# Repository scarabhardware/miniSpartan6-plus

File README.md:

# miniSpartan6-plus

## programming

```sh
# program fpga
xc3sprog -c ftdi dvid_serdes.bit
# program SPI flash
xc3sprog -c ftdi bscan_spi_s6lx9_ftg256.bit
xc3sprog -c ftdi -I dvid_serdes.bit
```

## references

 - http://www.scarabhardware.com
 - http://hamsterworks.co.nz/mediawiki/index.php/FPGA_Projects
 - https://github.com/timvideos/HDMI2USB

## board pinout

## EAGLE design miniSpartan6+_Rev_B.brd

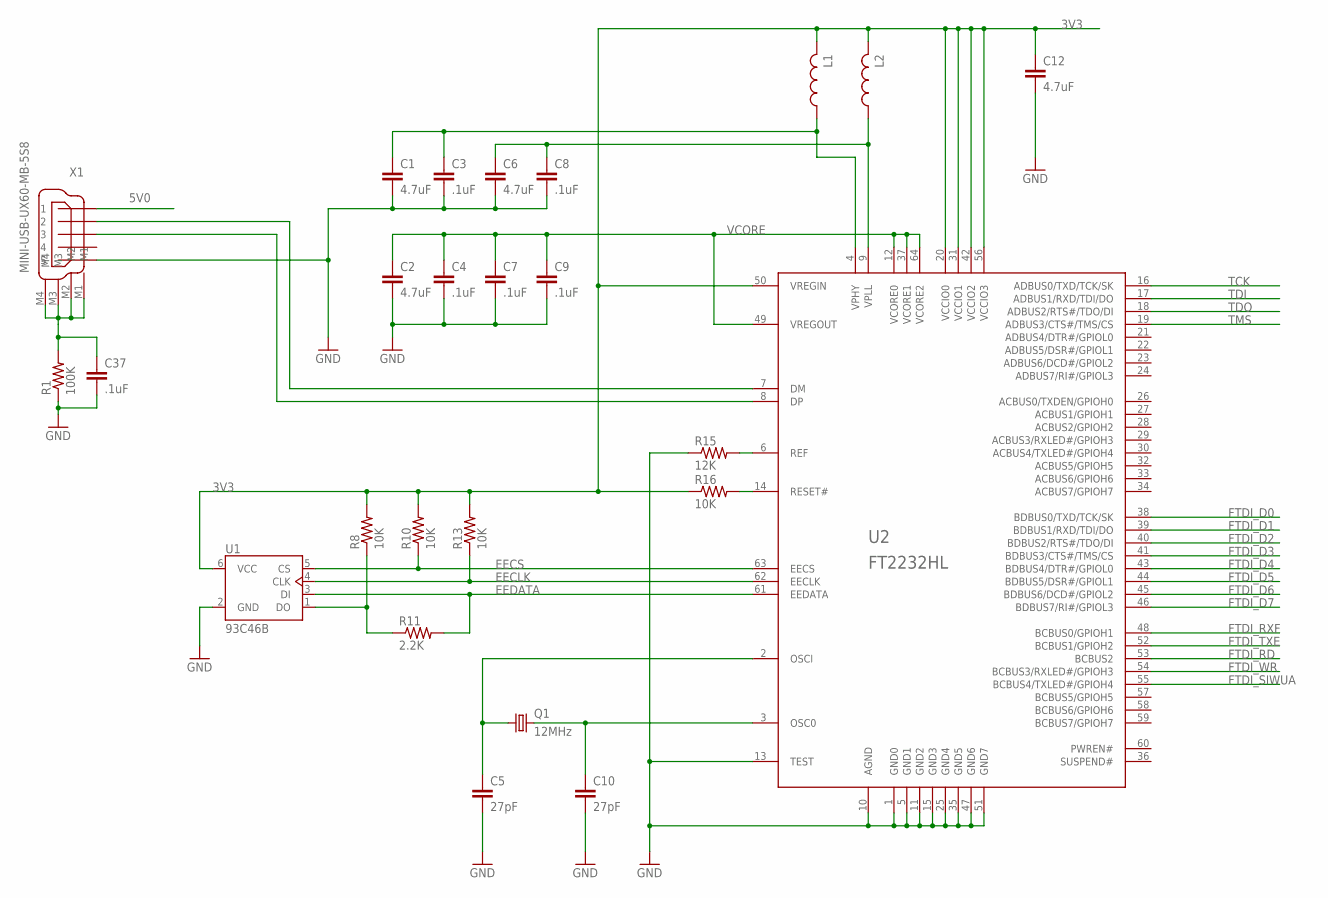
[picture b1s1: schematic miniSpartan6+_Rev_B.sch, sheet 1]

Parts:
C1, C2, C6, C12: 4.7uF; C0603K
C3, C4, C7, C8, C9, C37: .1uF; C0603K
C5, C10: 27pF; C0603K
L1, L2: L-USL2012C; L2012C
Q1: 12MHz; CRYSTAL3.2X2.5MM
R1: 100K; R0603
R8, R10, R13, R16: 10K; R0603
R11: 2.2K; R0603
R15: 12K; R0603
U1: 93C46B; SOT23-6
U2: FT2232HL; LQFP64
X1: MINI-USB-UX60-MB-5S8; UX60-MB-5S8

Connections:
3V3: C12.1, L1.2, L2.2, R8.2, R10.2, R13.2, R16.1, U1.6 (VCC), U2.20 (VCCIO0), U2.31 (VCCIO1), U2.42 (VCCIO2), U2.50 (VREGIN), U2.56 (VCCIO3); also elsewhere on the board
5V0: X1.1; also elsewhere on the board
EECLK: R13.1, U1.4 (CLK), U2.62 (EECLK)
EECS: R10.1, U1.5 (CS), U2.63 (EECS)
EEDATA: R11.2, U1.3 (DI), U2.61 (EEDATA)
FTDI_D0: U2.38 (BDBUS0/TXD/TCK/SK); also elsewhere on the board
FTDI_D1: U2.39 (BDBUS1/RXD/TDI/DO); also elsewhere on the board
FTDI_D2: U2.40 (BDBUS2/RTS#/TDO/DI); also elsewhere on the board
FTDI_D3: U2.41 (BDBUS3/CTS#/TMS/CS); also elsewhere on the board
FTDI_D4: U2.43 (BDBUS4/DTR#/GPIOL0); also elsewhere on the board
FTDI_D5: U2.44 (BDBUS5/DSR#/GPIOL1); also elsewhere on the board
FTDI_D6: U2.45 (BDBUS6/DCD#/GPIOL2); also elsewhere on the board
FTDI_D7: U2.46 (BDBUS7/RI#/GPIOL3); also elsewhere on the board
FTDI_RD: U2.53 (BCBUS2); also elsewhere on the board
FTDI_RXF: U2.48 (BCBUS0/GPIOH1); also elsewhere on the board
FTDI_SIWUA: U2.55 (BCBUS4/TXLED#/GPIOH4); also elsewhere on the board
FTDI_TXE: U2.52 (BCBUS1/GPIOH2); also elsewhere on the board
FTDI_WR: U2.54 (BCBUS3/RXLED#/GPIOH3); also elsewhere on the board
GND: C1.2, C2.2, C3.2, C4.2, C5.2, C6.2, C7.2, C8.2, C9.2, C10.2, C12.2, C37.2, R1.1, R15.1, U1.2 (GND), U2.1 (GND0), U2.5 (GND1), U2.10 (AGND), U2.11 (GND2), U2.13 (TEST), U2.15 (GND3), U2.25 (GND4), U2.35 (GND5), U2.47 (GND6), U2.51 (GND7), X1.5; also elsewhere on the board
unnamed: U2.7 (DM), X1.2
unnamed: C37.1, R1.2, X1.M1, X1.M2, X1.M3, X1.M4
unnamed: U2.8 (DP), X1.3
unnamed: C5.1, Q1.1, U2.2 (OSCI)
unnamed: C10.1, Q1.3 (2), U2.3 (OSC0)
unnamed: C6.1, C8.1, L2.1, U2.9 (VPLL)
unnamed: R16.2, U2.14 (RESET#)
unnamed: R15.2, U2.6 (REF)
unnamed: C1.1, C3.1, L1.1, U2.4 (VPHY)
unnamed: R8.1, R11.1, U1.1 (DO)
TCK: U2.16 (ADBUS0/TXD/TCK/SK); also elsewhere on the board
TDI: U2.17 (ADBUS1/RXD/TDI/DO); also elsewhere on the board
TDO: U2.18 (ADBUS2/RTS#/TDO/DI); also elsewhere on the board
TMS: U2.19 (ADBUS3/CTS#/TMS/CS); also elsewhere on the board
VCORE: C2.1, C4.1, C7.1, C9.1, U2.12 (VCORE0), U2.37 (VCORE1), U2.49 (VREGOUT), U2.64 (VCORE2)

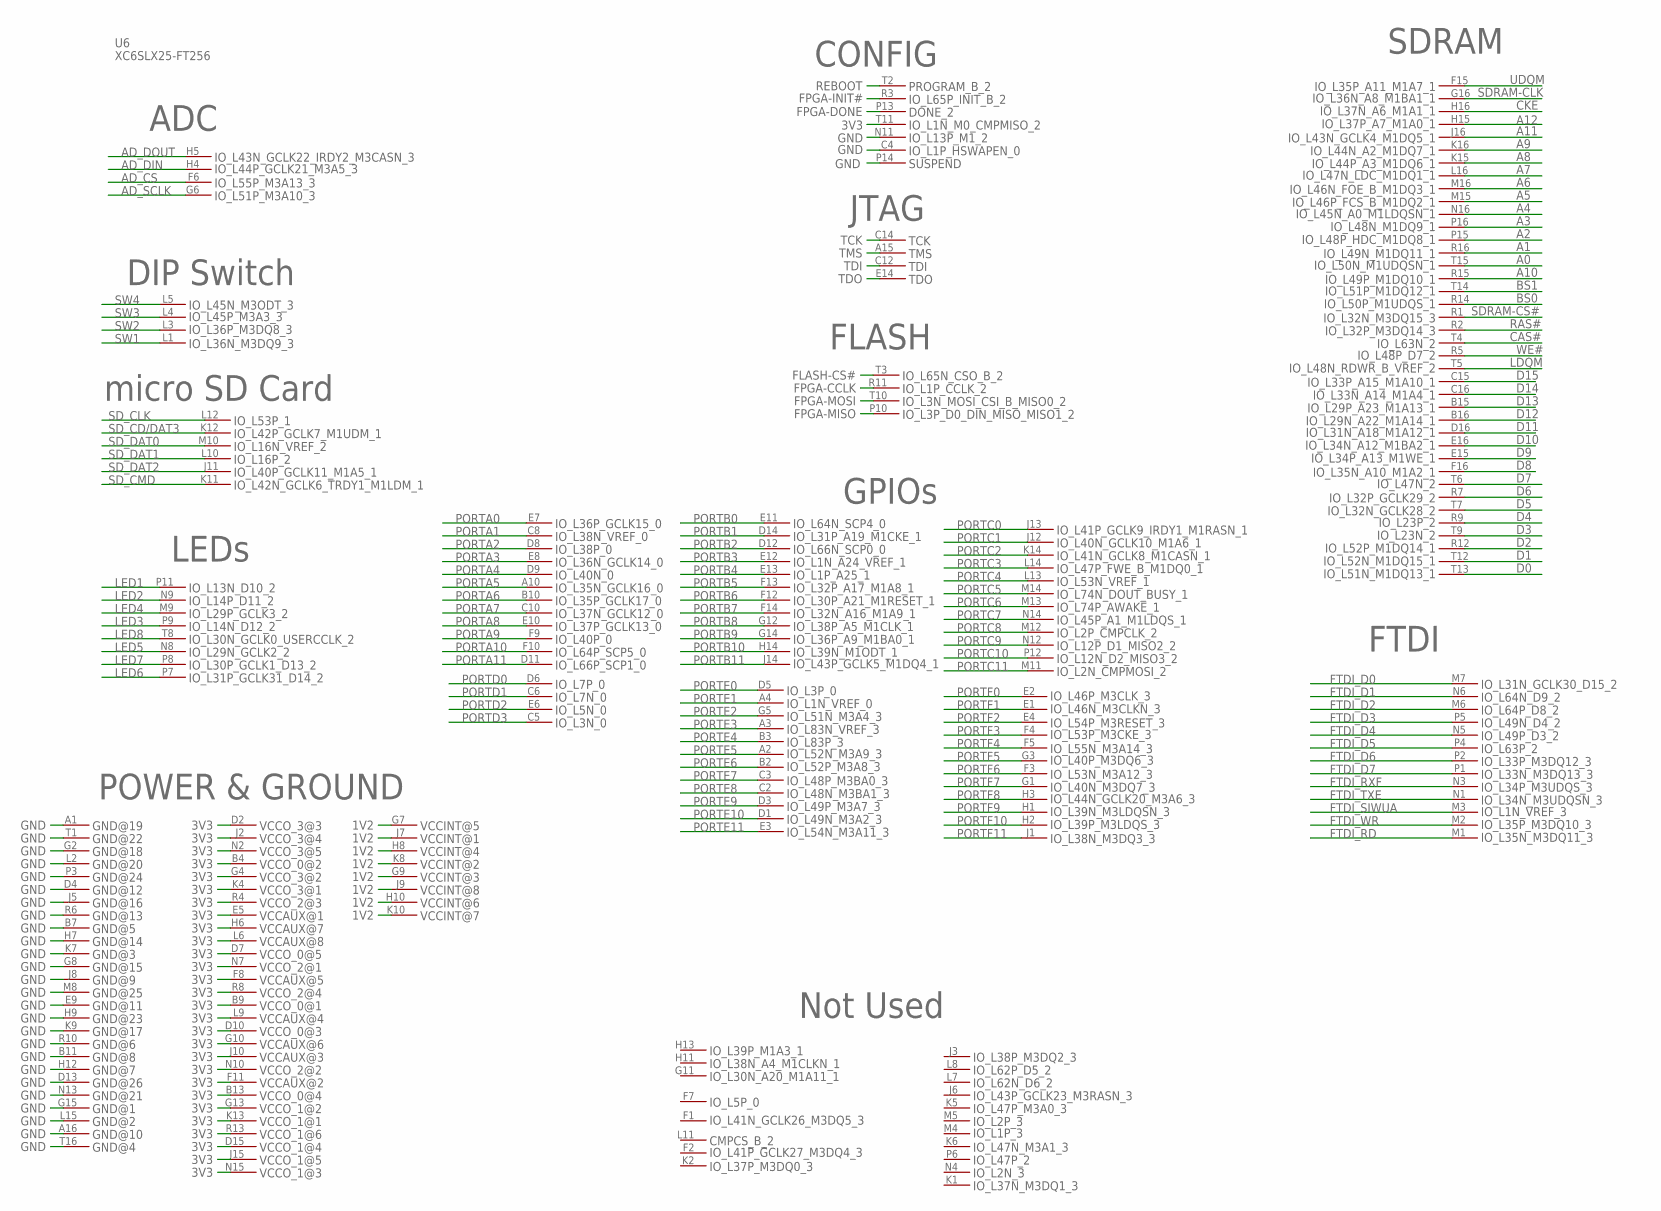
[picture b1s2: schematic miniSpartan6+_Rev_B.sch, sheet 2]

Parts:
U6: XC6SLX25-FT256; XILINX-FT256; DIGIKEY# 122-1753-ND

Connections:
1V2: U6.G7, U6.G9, U6.H8, U6.H10, U6.J7, U6.J9, U6.K8, U6.K10; also elsewhere on the board
3V3: U6.B4, U6.B9, U6.B13, U6.D2, U6.D7, U6.D10, U6.D15, U6.E5, U6.F8, U6.F11, U6.G4, U6.G10, U6.G13, U6.H6, U6.J2, U6.J10, U6.J15, U6.K4, U6.K13, U6.L6, U6.L9, U6.N2, U6.N7, U6.N10, U6.N15, U6.R4, U6.R8, U6.R13, U6.T11; also elsewhere on the board
A0: U6.T15; also elsewhere on the board
A1: U6.R16; also elsewhere on the board
A2: U6.P15; also elsewhere on the board
A3: U6.P16; also elsewhere on the board
A4: U6.N16; also elsewhere on the board
A5: U6.M15; also elsewhere on the board
A6: U6.M16; also elsewhere on the board
A7: U6.L16; also elsewhere on the board
A8: U6.K15; also elsewhere on the board
A9: U6.K16; also elsewhere on the board
A10: U6.R15; also elsewhere on the board
A11: U6.J16; also elsewhere on the board
A12: U6.H15; also elsewhere on the board
AD_CS: U6.F6; also elsewhere on the board
AD_DIN: U6.H4; also elsewhere on the board
AD_DOUT: U6.H5; also elsewhere on the board
AD_SCLK: U6.G6; also elsewhere on the board
BS0: U6.R14; also elsewhere on the board
BS1: U6.T14; also elsewhere on the board
CAS#: U6.T4; also elsewhere on the board
CKE: U6.H16; also elsewhere on the board
D0: U6.T13; also elsewhere on the board
D1: U6.T12; also elsewhere on the board
D2: U6.R12; also elsewhere on the board
D3: U6.T9; also elsewhere on the board
D4: U6.R9; also elsewhere on the board
D5: U6.T7; also elsewhere on the board
D6: U6.R7; also elsewhere on the board
D7: U6.T6; also elsewhere on the board
D8: U6.F16; also elsewhere on the board
D9: U6.E15; also elsewhere on the board
D10: U6.E16; also elsewhere on the board
D11: U6.D16; also elsewhere on the board
D12: U6.B16; also elsewhere on the board
D13: U6.B15; also elsewhere on the board
D14: U6.C16; also elsewhere on the board
D15: U6.C15; also elsewhere on the board
FLASH-CS#: U6.T3; also elsewhere on the board
FPGA-CCLK: U6.R11; also elsewhere on the board
FPGA-DONE: U6.P13
FPGA-INIT#: U6.R3
FPGA-MISO: U6.P10; also elsewhere on the board
FPGA-MOSI: U6.T10; also elsewhere on the board
FTDI_D0: U6.M7; also elsewhere on the board
FTDI_D1: U6.N6; also elsewhere on the board
FTDI_D2: U6.M6; also elsewhere on the board
FTDI_D3: U6.P5; also elsewhere on the board
FTDI_D4: U6.N5; also elsewhere on the board
FTDI_D5: U6.P4; also elsewhere on the board
FTDI_D6: U6.P2; also elsewhere on the board
FTDI_D7: U6.P1; also elsewhere on the board
FTDI_RD: U6.M1; also elsewhere on the board
FTDI_RXF: U6.N3; also elsewhere on the board
FTDI_SIWUA: U6.M3; also elsewhere on the board
FTDI_TXE: U6.N1; also elsewhere on the board
FTDI_WR: U6.M2; also elsewhere on the board
GND: U6.A1, U6.A16, U6.B7, U6.B11, U6.C4, U6.D4, U6.D13, U6.E9, U6.G2, U6.G8, U6.G15, U6.H7, U6.H9, U6.H12, U6.J5, U6.J8, U6.K7, U6.K9, U6.L2, U6.L15, U6.M8, U6.N11, U6.N13, U6.P3, U6.P14, U6.R6, U6.R10, U6.T1, U6.T16; also elsewhere on the board
LDQM: U6.T5; also elsewhere on the board
LED1: U6.P11; also elsewhere on the board
LED2: U6.N9; also elsewhere on the board
LED3: U6.P9; also elsewhere on the board
LED4: U6.M9; also elsewhere on the board
LED5: U6.N8; also elsewhere on the board
LED6: U6.P7; also elsewhere on the board
LED7: U6.P8; also elsewhere on the board
LED8: U6.T8; also elsewhere on the board
PORTA0: U6.E7; also elsewhere on the board
PORTA1: U6.C8; also elsewhere on the board
PORTA2: U6.D8; also elsewhere on the board
PORTA3: U6.E8; also elsewhere on the board
PORTA4: U6.D9; also elsewhere on the board
PORTA5: U6.A10; also elsewhere on the board
PORTA6: U6.B10; also elsewhere on the board
PORTA7: U6.C10; also elsewhere on the board
PORTA8: U6.E10; also elsewhere on the board
PORTA9: U6.F9; also elsewhere on the board
PORTA10: U6.F10; also elsewhere on the board
PORTA11: U6.D11; also elsewhere on the board
PORTB0: U6.E11; also elsewhere on the board
PORTB1: U6.D14; also elsewhere on the board
PORTB2: U6.D12; also elsewhere on the board
PORTB3: U6.E12; also elsewhere on the board
PORTB4: U6.E13; also elsewhere on the board
PORTB5: U6.F13; also elsewhere on the board
PORTB6: U6.F12; also elsewhere on the board
PORTB7: U6.F14; also elsewhere on the board
PORTB8: U6.G12; also elsewhere on the board
PORTB9: U6.G14; also elsewhere on the board
PORTB10: U6.H14; also elsewhere on the board
PORTB11: U6.J14; also elsewhere on the board
PORTC0: U6.J13; also elsewhere on the board
PORTC1: U6.J12; also elsewhere on the board
PORTC2: U6.K14; also elsewhere on the board
PORTC3: U6.L14; also elsewhere on the board
PORTC4: U6.L13; also elsewhere on the board
PORTC5: U6.M14; also elsewhere on the board
PORTC6: U6.M13; also elsewhere on the board
PORTC7: U6.N14; also elsewhere on the board
PORTC8: U6.M12; also elsewhere on the board
PORTC9: U6.N12; also elsewhere on the board
PORTC10: U6.P12; also elsewhere on the board
PORTC11: U6.M11; also elsewhere on the board
PORTD0: U6.D6; also elsewhere on the board
PORTD1: U6.C6; also elsewhere on the board
PORTD2: U6.E6; also elsewhere on the board
PORTD3: U6.C5; also elsewhere on the board
PORTE0: U6.D5; also elsewhere on the board
PORTE1: U6.A4; also elsewhere on the board
PORTE2: U6.G5; also elsewhere on the board
PORTE3: U6.A3; also elsewhere on the board
PORTE4: U6.B3; also elsewhere on the board
PORTE5: U6.A2; also elsewhere on the board
PORTE6: U6.B2; also elsewhere on the board
PORTE7: U6.C3; also elsewhere on the board
PORTE8: U6.C2; also elsewhere on the board
PORTE9: U6.D3; also elsewhere on the board
PORTE10: U6.D1; also elsewhere on the board
PORTE11: U6.E3; also elsewhere on the board
PORTF0: U6.E2; also elsewhere on the board
PORTF1: U6.E1; also elsewhere on the board
PORTF2: U6.E4; also elsewhere on the board
PORTF3: U6.F4; also elsewhere on the board
PORTF4: U6.F5; also elsewhere on the board
PORTF5: U6.G3; also elsewhere on the board
PORTF6: U6.F3; also elsewhere on the board
PORTF7: U6.G1; also elsewhere on the board
PORTF8: U6.H3; also elsewhere on the board
PORTF9: U6.H1; also elsewhere on the board
PORTF10: U6.H2; also elsewhere on the board
PORTF11: U6.J1; also elsewhere on the board
RAS#: U6.R2; also elsewhere on the board
REBOOT: U6.T2; also elsewhere on the board
SDRAM-CLK: U6.G16; also elsewhere on the board
SDRAM-CS#: U6.R1; also elsewhere on the board
SD_CD/DAT3: U6.K12; also elsewhere on the board
SD_CLK: U6.L12; also elsewhere on the board
SD_CMD: U6.K11; also elsewhere on the board
SD_DAT0: U6.M10; also elsewhere on the board
SD_DAT1: U6.L10; also elsewhere on the board
SD_DAT2: U6.J11; also elsewhere on the board
SW1: U6.L1; also elsewhere on the board
SW2: U6.L3; also elsewhere on the board
SW3: U6.L4; also elsewhere on the board
SW4: U6.L5; also elsewhere on the board
TCK: U6.C14; also elsewhere on the board
TDI: U6.C12; also elsewhere on the board
TDO: U6.E14; also elsewhere on the board
TMS: U6.A15; also elsewhere on the board
UDQM: U6.F15; also elsewhere on the board
WE#: U6.R5; also elsewhere on the board

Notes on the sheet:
SDRAM
POWER & GROUND
JTAG
FLASH
CONFIG
FTDI
DIP Switch
micro SD Card
LEDs
GPIOs
Not Used
ADC

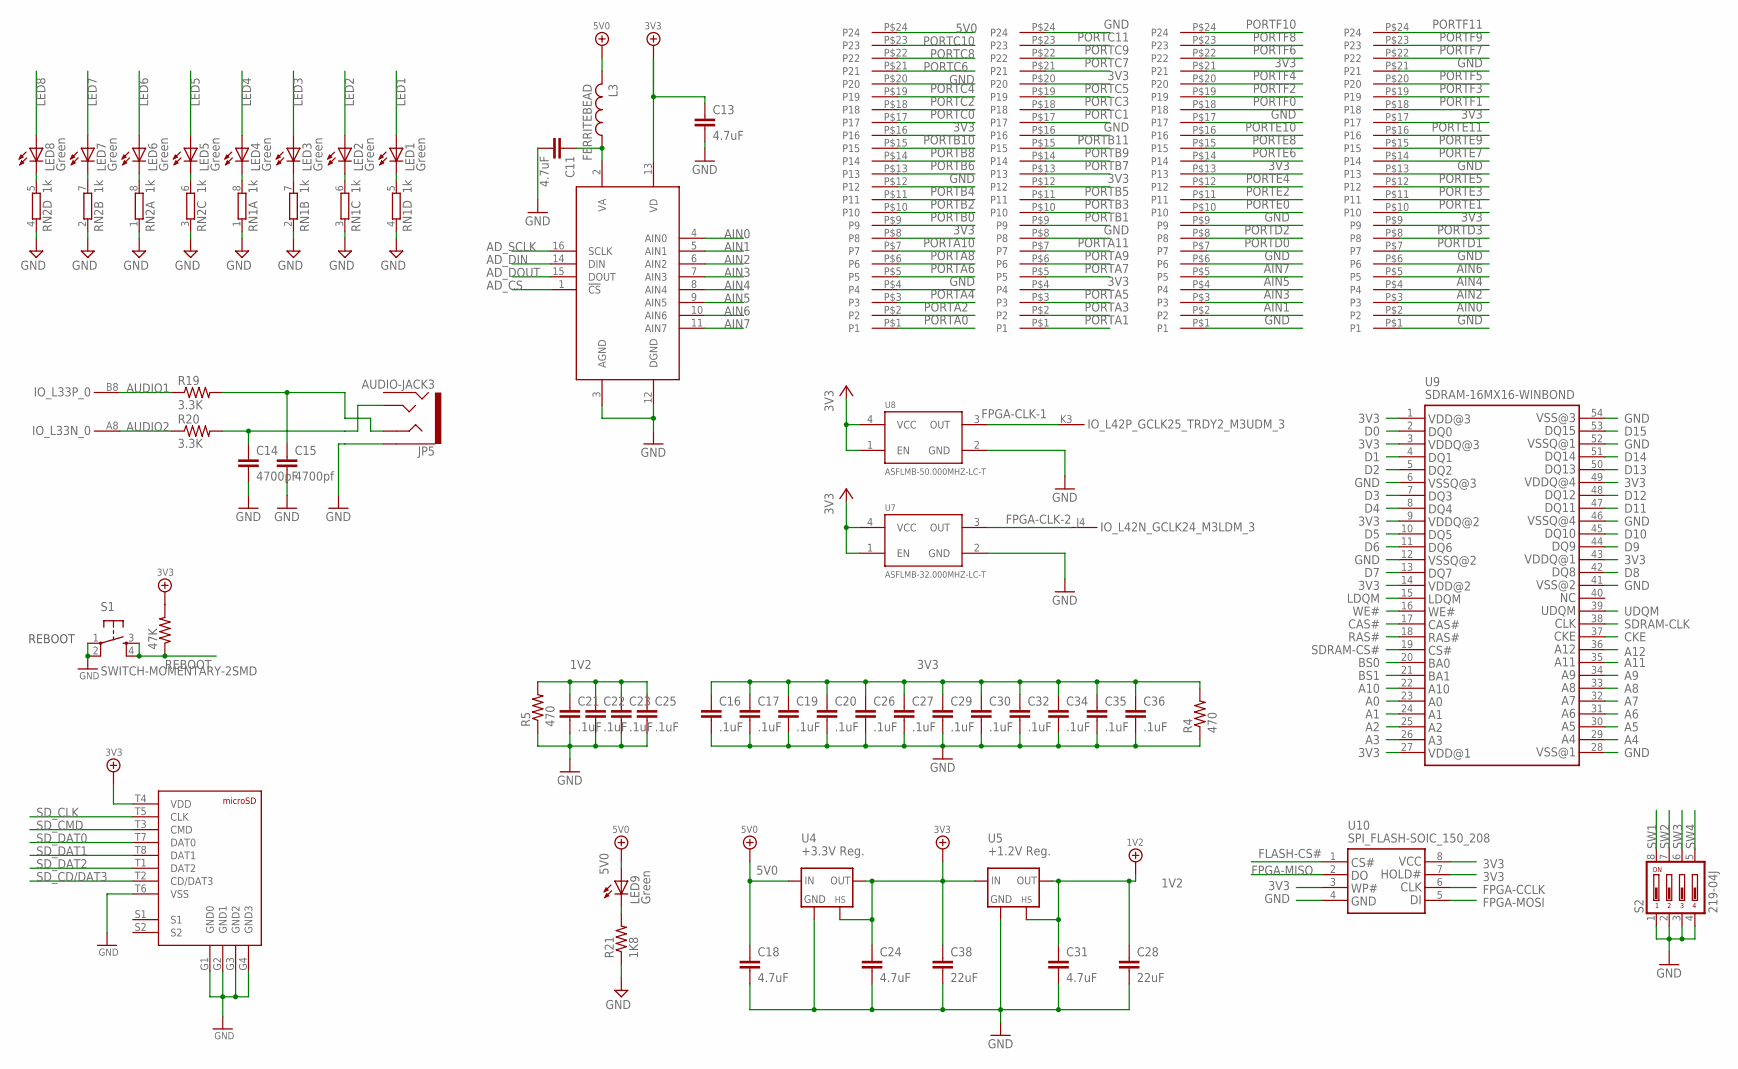
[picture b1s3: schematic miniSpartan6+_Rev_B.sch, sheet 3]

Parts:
C11, C13: 4.7uF; C0603K
C14: 4700pF; C0603K
C15: 4700pf; C0603K
C16, C17, C19, C20, C21, C22, C23, C25, C26, C27, C29, C30, C32, C34, C35, C36: .1uF; C0603K
C18, C24, C31: 4.7uF; C0603K; MOUSER# 81-GRM188F51A475ZE20; DIGIKEY# 490-3302-1-ND
C28, C38: 22uF; C0603K; MOUSER# 81-GRM188F51A475ZE20; DIGIKEY# 490-3302-1-ND
J4, J6: P24-1; 1X24
J5: MICROSD_MOLEX; MICROSD_104031
JP5: AUDIO-JACK3; AUDIO-JACK-TRRS-SMD
L3: FERRITEBEAD; L2012C
LED1, LED2, LED3, LED4, LED5, LED6, LED7, LED8, LED9: Green; SML0603
R4, R5: 470; R0603
R18: 47K; R0603
R19, R20: 3.3K; R0603
R21: 1K8; R0603
RN1, RN2: 1k; 0603-ARV
S1: SWITCH-MOMENTARY-2SMD; TACTILE_SWITCH_SMD
S2: 219-04J; CTS-219-04J
U3: ADC088S102CIMT; TSSOP16
U4: +3.3V Reg.; SOT223; MOUSER# 522-ZLDO1117G33TA; DIGIKEY# ZLDO1117G33DICT-ND
U5: +1.2V Reg.; SOT223; MOUSER# 522-ZLDO1117G12TA; DIGIKEY# ZLDO1117G12DICT-ND
U6: XC6SLX25-FT256; XILINX-FT256; DIGIKEY# 122-1753-ND
U7: ASFLMB-32.000MHZ-LC-T; CRYSTAL-OSC-SMD-5X3
U8: ASFLMB-50.000MHZ-LC-T; CRYSTAL-OSC-SMD-5X3
U9: SDRAM-16MX16-WINBOND; TSOPII-54
U10: SPI_FLASH-SOIC_150_208; SPI-8_SOIC_150_208; DIGIKEY# W25Q80BVSNIG-ND
U$7, U$8: P24-1; 1X24

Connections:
1V2: C21.1, C22.1, C23.1, C25.1, C28.1, C31.1, R5.2, U5.2 (OUT), U5.4 (HS); also elsewhere on the board
3V3: C13.1, C16.1, C17.1, C19.1, C20.1, C24.1, C26.1, C27.1, C29.1, C30.1, C32.1, C34.1, C35.1, C36.1, C38.1, J4.P$13 (P13), J4.P$21 (P21), J5.T4 (VDD), J6.P$9 (P9), J6.P$17 (P17), R4.2, R18.2, U3.13 (VD), U4.2 (OUT), U4.4 (HS), U5.3 (IN), U7.1 (EN), U7.4 (VCC), U8.1 (EN), U8.4 (VCC), U9.1, U9.3, U9.9, U9.14, U9.27, U9.43, U9.49, U10.3, U10.7, U10.8, U$7.P$8 (P8), U$7.P$16 (P16), U$8.P$4 (P4), U$8.P$12 (P12), U$8.P$20 (P20); also elsewhere on the board
5V0: C18.1, L3.2, LED9.A, U4.3 (IN), U$7.P$24 (P24); also elsewhere on the board
A0: U9.23; also elsewhere on the board
A1: U9.24; also elsewhere on the board
A2: U9.25; also elsewhere on the board
A3: U9.26; also elsewhere on the board
A4: U9.29; also elsewhere on the board
A5: U9.30; also elsewhere on the board
A6: U9.31; also elsewhere on the board
A7: U9.32; also elsewhere on the board
A8: U9.33; also elsewhere on the board
A9: U9.34; also elsewhere on the board
A10: U9.22; also elsewhere on the board
A11: U9.35; also elsewhere on the board
A12: U9.36; also elsewhere on the board
AD_CS: U3.1 (!CS); also elsewhere on the board
AD_DIN: U3.14 (DIN); also elsewhere on the board
AD_DOUT: U3.15 (DOUT); also elsewhere on the board
AD_SCLK: U3.16 (SCLK); also elsewhere on the board
AIN0: J6.P$2 (P2), U3.4 (AIN0)
AIN1: J4.P$2 (P2), U3.5 (AIN1)
AIN2: J6.P$3 (P3), U3.6 (AIN2)
AIN3: J4.P$3 (P3), U3.7 (AIN3)
AIN4: J6.P$4 (P4), U3.8 (AIN4)
AIN5: J4.P$4 (P4), U3.9 (AIN5)
AIN6: J6.P$5 (P5), U3.10 (AIN6)
AIN7: J4.P$5 (P5), U3.11 (AIN7)
AUDIO1: R19.1, U6.B8
AUDIO2: R20.1, U6.A8
BS0: U9.20; also elsewhere on the board
BS1: U9.21; also elsewhere on the board
CAS#: U9.17; also elsewhere on the board
CKE: U9.37; also elsewhere on the board
D0: U9.2; also elsewhere on the board
D1: U9.4; also elsewhere on the board
D2: U9.5; also elsewhere on the board
D3: U9.7; also elsewhere on the board
D4: U9.8; also elsewhere on the board
D5: U9.10; also elsewhere on the board
D6: U9.11; also elsewhere on the board
D7: U9.13; also elsewhere on the board
D8: U9.42; also elsewhere on the board
D9: U9.44; also elsewhere on the board
D10: U9.45; also elsewhere on the board
D11: U9.47; also elsewhere on the board
D12: U9.48; also elsewhere on the board
D13: U9.50; also elsewhere on the board
D14: U9.51; also elsewhere on the board
D15: U9.53; also elsewhere on the board
FLASH-CS#: U10.1; also elsewhere on the board
FPGA-CCLK: U10.6; also elsewhere on the board
FPGA-CLK-1: U6.K3, U8.3 (OUT)
FPGA-CLK-2: U6.J4, U7.3 (OUT)
FPGA-MISO: U10.2; also elsewhere on the board
FPGA-MOSI: U10.5; also elsewhere on the board
GND: C11.2, C13.2, C14.2, C15.2, C16.2, C17.2, C18.2, C19.2, C20.2, C21.2, C22.2, C23.2, C24.2, C25.2, C26.2, C27.2, C28.2, C29.2, C30.2, C31.2, C32.2, C34.2, C35.2, C36.2, C38.2, J4.P$1 (P1), J4.P$6 (P6), J4.P$9 (P9), J4.P$17 (P17), J5.G1 (GND0), J5.G2 (GND1), J5.G3 (GND2), J5.G4 (GND3), J5.T6 (VSS), J6.P$1 (P1), J6.P$6 (P6), J6.P$13 (P13), J6.P$21 (P21), JP5.EARTH, R4.1, R5.1, R21.1, RN1.1, RN1.2 (1), RN1.3 (1), RN1.4 (1), RN2.1, RN2.2 (1), RN2.3 (1), RN2.4 (1), S1.1, S1.2, S2.1, S2.2, S2.3, S2.4, U3.3 (AGND), U3.12 (DGND), U4.1 (GND), U5.1 (GND), U7.2 (GND), U8.2 (GND), U9.6, U9.12, U9.28, U9.41, U9.46, U9.52, U9.54, U10.4, U$7.P$4 (P4), U$7.P$12 (P12), U$7.P$20 (P20), U$8.P$8 (P8), U$8.P$16 (P16), U$8.P$24 (P24); also elsewhere on the board
LDQM: U9.15; also elsewhere on the board
LED1: LED1.A; also elsewhere on the board
LED2: LED2.A; also elsewhere on the board
LED3: LED3.A; also elsewhere on the board
LED4: LED4.A; also elsewhere on the board
LED5: LED5.A; also elsewhere on the board
LED6: LED6.A; also elsewhere on the board
LED7: LED7.A; also elsewhere on the board
LED8: LED8.A; also elsewhere on the board
unnamed: LED9.C, R21.2
unnamed: C11.1, L3.1, U3.2 (VA)
unnamed: LED1.C, RN1.5 (2)
unnamed: LED2.C, RN1.6 (2)
unnamed: LED3.C, RN1.7 (2)
unnamed: LED4.C, RN1.8 (2)
unnamed: LED5.C, RN2.6 (2)
unnamed: LED6.C, RN2.8 (2)
unnamed: LED7.C, RN2.7 (2)
unnamed: LED8.C, RN2.5 (2)
unnamed: C14.1, JP5.TIP, R20.2
unnamed: C15.1, JP5.RING1, R19.2
PORTA0: U$7.P$1 (P1); also elsewhere on the board
PORTA1: U$8.P$1 (P1); also elsewhere on the board
PORTA2: U$7.P$2 (P2); also elsewhere on the board
PORTA3: U$8.P$2 (P2); also elsewhere on the board
PORTA4: U$7.P$3 (P3); also elsewhere on the board
PORTA5: U$8.P$3 (P3); also elsewhere on the board
PORTA6: U$7.P$5 (P5); also elsewhere on the board
PORTA7: U$8.P$5 (P5); also elsewhere on the board
PORTA8: U$7.P$6 (P6); also elsewhere on the board
PORTA9: U$8.P$6 (P6); also elsewhere on the board
PORTA10: U$7.P$7 (P7); also elsewhere on the board
PORTA11: U$8.P$7 (P7); also elsewhere on the board
PORTB0: U$7.P$9 (P9); also elsewhere on the board
PORTB1: U$8.P$9 (P9); also elsewhere on the board
PORTB2: U$7.P$10 (P10); also elsewhere on the board
PORTB3: U$8.P$10 (P10); also elsewhere on the board
PORTB4: U$7.P$11 (P11); also elsewhere on the board
PORTB5: U$8.P$11 (P11); also elsewhere on the board
PORTB6: U$7.P$13 (P13); also elsewhere on the board
PORTB7: U$8.P$13 (P13); also elsewhere on the board
PORTB8: U$7.P$14 (P14); also elsewhere on the board
PORTB9: U$8.P$14 (P14); also elsewhere on the board
PORTB10: U$7.P$15 (P15); also elsewhere on the board
PORTB11: U$8.P$15 (P15); also elsewhere on the board
PORTC0: U$7.P$17 (P17); also elsewhere on the board
PORTC1: U$8.P$17 (P17); also elsewhere on the board
PORTC2: U$7.P$18 (P18); also elsewhere on the board
PORTC3: U$8.P$18 (P18); also elsewhere on the board
PORTC4: U$7.P$19 (P19); also elsewhere on the board
PORTC5: U$8.P$19 (P19); also elsewhere on the board
PORTC6: U$7.P$21 (P21); also elsewhere on the board
PORTC7: U$8.P$21 (P21); also elsewhere on the board
PORTC8: U$7.P$22 (P22); also elsewhere on the board
PORTC9: U$8.P$22 (P22); also elsewhere on the board
PORTC10: U$7.P$23 (P23); also elsewhere on the board
PORTC11: U$8.P$23 (P23); also elsewhere on the board
PORTD0: J4.P$7 (P7); also elsewhere on the board
PORTD1: J6.P$7 (P7); also elsewhere on the board
PORTD2: J4.P$8 (P8); also elsewhere on the board
PORTD3: J6.P$8 (P8); also elsewhere on the board
PORTE0: J4.P$10 (P10); also elsewhere on the board
PORTE1: J6.P$10 (P10); also elsewhere on the board
PORTE2: J4.P$11 (P11); also elsewhere on the board
PORTE3: J6.P$11 (P11); also elsewhere on the board
PORTE4: J4.P$12 (P12); also elsewhere on the board
PORTE5: J6.P$12 (P12); also elsewhere on the board
PORTE6: J4.P$14 (P14); also elsewhere on the board
PORTE7: J6.P$14 (P14); also elsewhere on the board
PORTE8: J4.P$15 (P15); also elsewhere on the board
PORTE9: J6.P$15 (P15); also elsewhere on the board
PORTE10: J4.P$16 (P16); also elsewhere on the board
PORTE11: J6.P$16 (P16); also elsewhere on the board
PORTF0: J4.P$18 (P18); also elsewhere on the board
PORTF1: J6.P$18 (P18); also elsewhere on the board
PORTF2: J4.P$19 (P19); also elsewhere on the board
PORTF3: J6.P$19 (P19); also elsewhere on the board
PORTF4: J4.P$20 (P20); also elsewhere on the board
PORTF5: J6.P$20 (P20); also elsewhere on the board
PORTF6: J4.P$22 (P22); also elsewhere on the board
PORTF7: J6.P$22 (P22); also elsewhere on the board
PORTF8: J4.P$23 (P23); also elsewhere on the board
PORTF9: J6.P$23 (P23); also elsewhere on the board
PORTF10: J4.P$24 (P24); also elsewhere on the board
PORTF11: J6.P$24 (P24); also elsewhere on the board
RAS#: U9.18; also elsewhere on the board
REBOOT: R18.1, S1.3, S1.4; also elsewhere on the board
SDRAM-CLK: U9.38; also elsewhere on the board
SDRAM-CS#: U9.19; also elsewhere on the board
SD_CD/DAT3: J5.T2 (CD/DAT3); also elsewhere on the board
SD_CLK: J5.T5 (CLK); also elsewhere on the board
SD_CMD: J5.T3 (CMD); also elsewhere on the board
SD_DAT0: J5.T7 (DAT0); also elsewhere on the board
SD_DAT1: J5.T8 (DAT1); also elsewhere on the board
SD_DAT2: J5.T1 (DAT2); also elsewhere on the board
SW1: S2.8; also elsewhere on the board
SW2: S2.7; also elsewhere on the board
SW3: S2.6; also elsewhere on the board
SW4: S2.5; also elsewhere on the board
UDQM: U9.39; also elsewhere on the board
WE#: U9.16; also elsewhere on the board

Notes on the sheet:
REBOOT

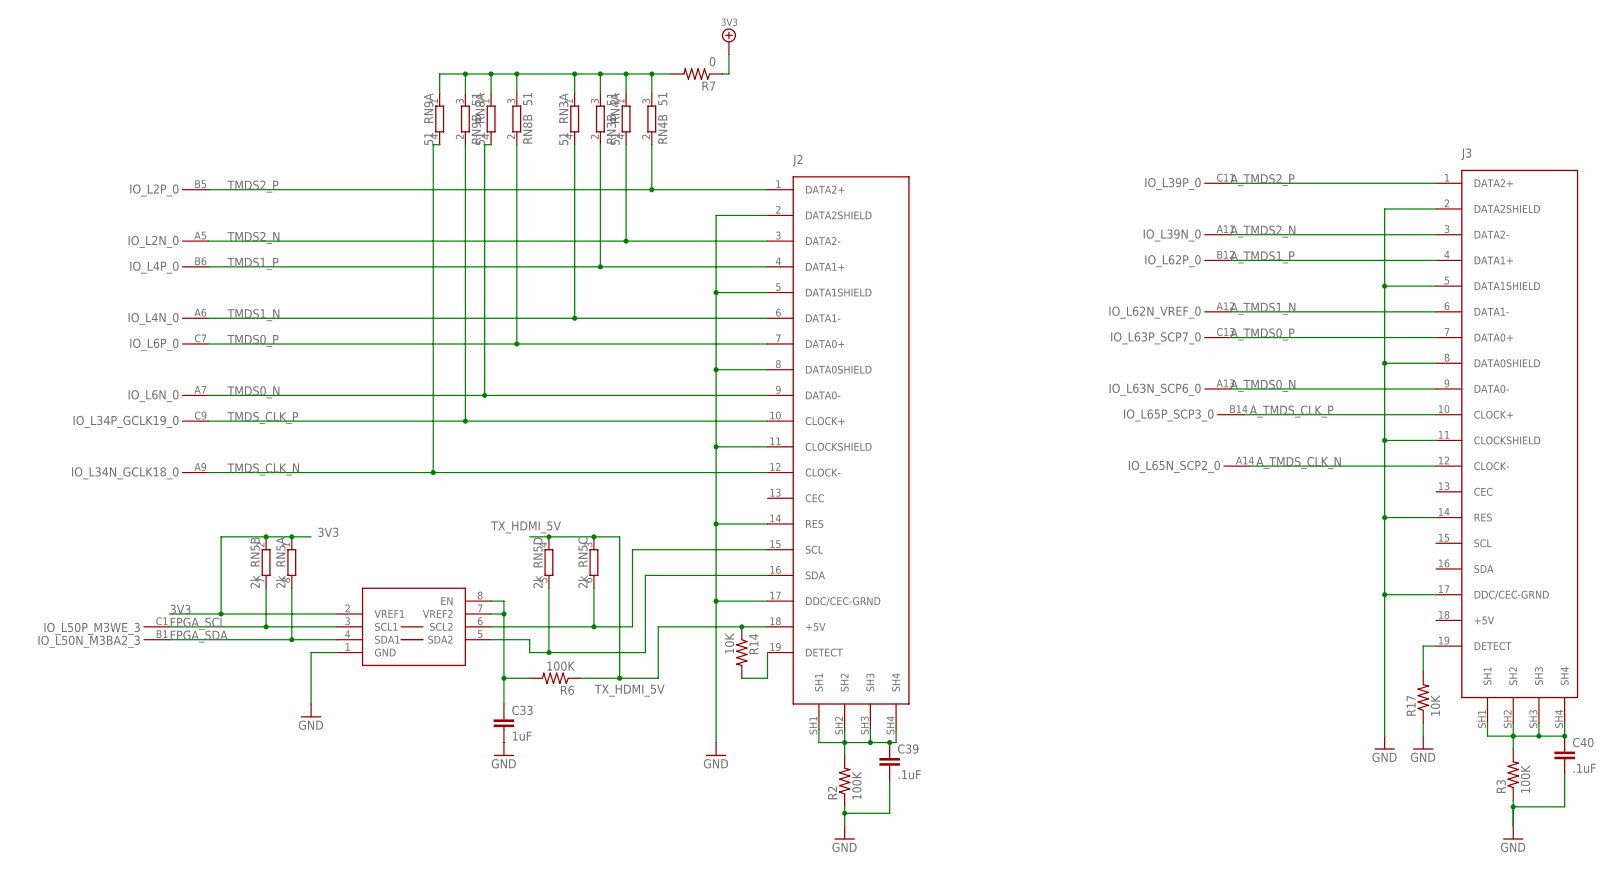
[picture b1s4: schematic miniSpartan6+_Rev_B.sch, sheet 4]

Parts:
C33: 1uF; C0603K
C39, C40: .1uF; C0603K
J2, J3: HDMI-TYPE-A-RECEPTICALFCI10029449; FCI-HDMI-TYPE-A-RECEPT
R2, R3, R6: 100K; R0603
R7: 0; R0603
R14, R17: 10K; R0603
RN3, RN4, RN8, RN9: 51; EXB34V
RN5: 2k; 0603-ARV
U6: XC6SLX25-FT256; XILINX-FT256; DIGIKEY# 122-1753-ND
U11: PCA9306; PSOP-8

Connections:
3V3: R7.1, RN5.1, RN5.2 (1), U11.2 (VREF1); also elsewhere on the board
A_TMDS0_N: J3.9 (DATA0-), U6.A13
A_TMDS0_P: J3.7 (DATA0+), U6.C13
A_TMDS1_N: J3.6 (DATA1-), U6.A12
A_TMDS1_P: J3.4 (DATA1+), U6.B12
A_TMDS2_N: J3.3 (DATA2-), U6.A11
A_TMDS2_P: J3.1 (DATA2+), U6.C11
A_TMDS_CLK_N: J3.12 (CLOCK-), U6.A14
A_TMDS_CLK_P: J3.10 (CLOCK+), U6.B14
DDC_SCL: J2.15 (SCL), RN5.6 (2), U11.6 (SCL2)
DDC_SDA: J2.16 (SDA), RN5.5 (2), U11.5 (SDA2)
DETECT1: J3.19 (DETECT), R17.2
DETECT2: J2.19 (DETECT), R14.2
FPGA_SCL: RN5.7 (2), U6.C1, U11.3 (SCL1)
FPGA_SDA: RN5.8 (2), U6.B1, U11.4 (SDA1)
GND: C33.2, C39.2, C40.2, J2.2 (DATA2SHIELD), J2.5 (DATA1SHIELD), J2.8 (DATA0SHIELD), J2.11 (CLOCKSHIELD), J2.14 (RES), J2.17 (DDC/CEC-GRND), J3.2 (DATA2SHIELD), J3.5 (DATA1SHIELD), J3.8 (DATA0SHIELD), J3.11 (CLOCKSHIELD), J3.14 (RES), J3.17 (DDC/CEC-GRND), R2.1, R3.1, R17.1, U11.1 (GND); also elsewhere on the board
unnamed: R7.2, RN3.1, RN3.3 (2), RN4.1, RN4.3 (2), RN8.1, RN8.3 (2), RN9.1, RN9.3 (2)
unnamed: C33.1, R6.2, U11.7 (VREF2), U11.8 (EN)
unnamed: C39.1, J2.SH1, J2.SH2, J2.SH3, J2.SH4, R2.2
unnamed: C40.1, J3.SH1, J3.SH2, J3.SH3, J3.SH4, R3.2
TMDS0_N: J2.9 (DATA0-), RN8.4 (2), U6.A7
TMDS0_P: J2.7 (DATA0+), RN8.2 (1), U6.C7
TMDS1_N: J2.6 (DATA1-), RN3.4 (2), U6.A6
TMDS1_P: J2.4 (DATA1+), RN3.2 (1), U6.B6
TMDS2_N: J2.3 (DATA2-), RN4.4 (2), U6.A5
TMDS2_P: J2.1 (DATA2+), RN4.2 (1), U6.B5
TMDS_CLK_N: J2.12 (CLOCK-), RN9.4 (2), U6.A9
TMDS_CLK_P: J2.10 (CLOCK+), RN9.2 (1), U6.C9
TX_HDMI_5V: J2.18 (+5V), R6.1, R14.1, RN5.3 (1), RN5.4 (1)

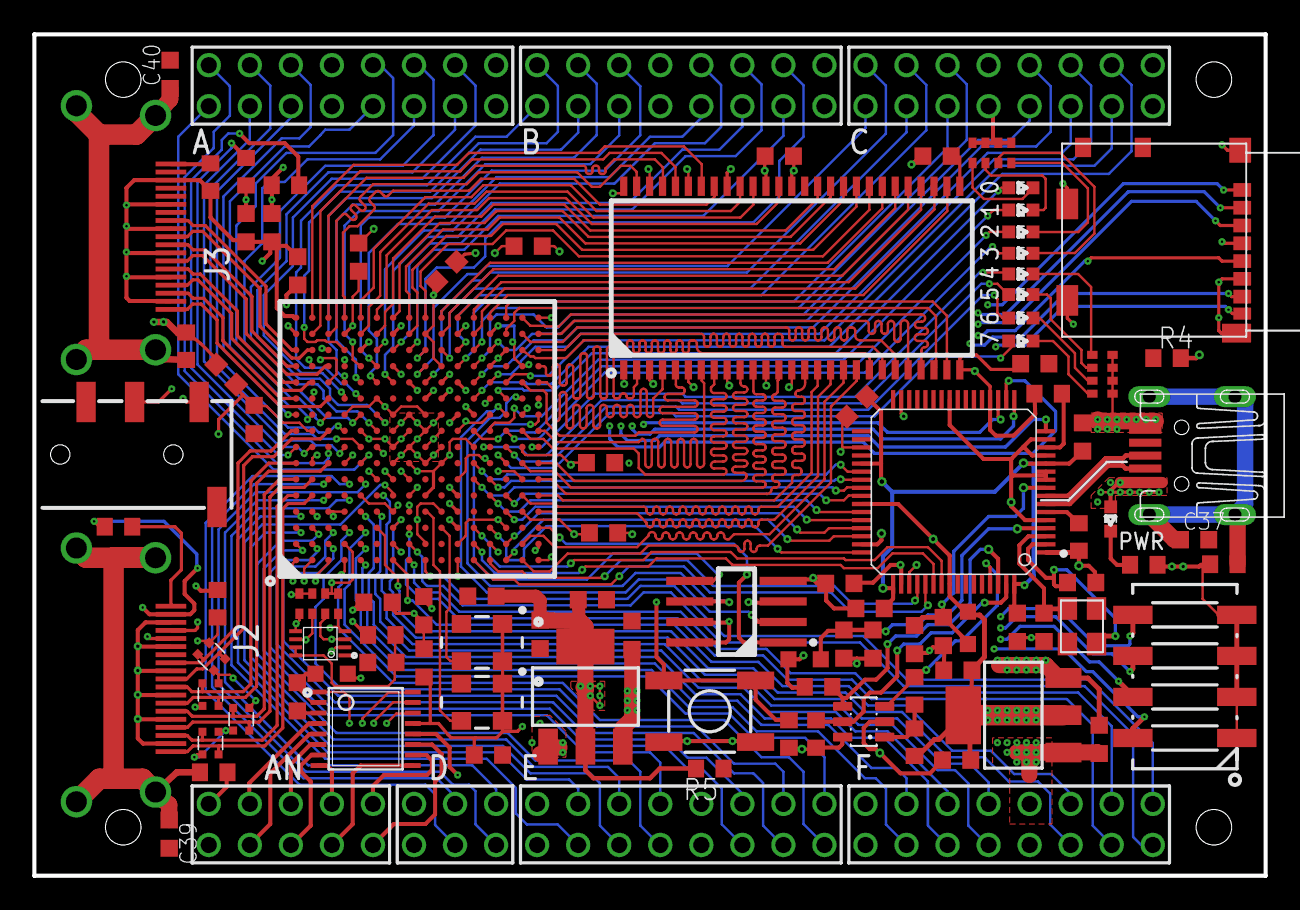
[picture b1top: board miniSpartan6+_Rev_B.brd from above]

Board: 4 copper layers, 76.2 x 52.1 mm, 101 parts (0 on the bottom side), 216 nets.

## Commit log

2014-08-01 Adding schematic and PCB for Revision B
2014-08-01 Fixed pdf
2014-08-02 More detailed pdf
2014-10-30 Updating to the current production version
2014-11-11 Adding HDMI projects
2015-01-21 Create miniSpartan6-plus.ucf
    Created master UCF file for miniSpartan6+.
2015-01-21 Added pins for flash memory.
2015-01-21 Added audio pins.
2015-01-25 Added bscan files for writing SPI flash
2015-01-25 Adding project as is from:
    http://hamsterworks.co.nz/mediawiki/images/2/22/Dvid_logo.zip
2015-01-25 Adding logo.c for changing logo from:
    http://hamsterworks.co.nz/mediawiki/index.php/MiniSpartan6%2B_DVID_Logo
    - Open the image in MS-Paint.
    - Resize the graphic to 128x128
    - Save it as a 24-bit BMP file
    - Use logo.c to dump out the pixel colours in a format that can be used to replace the data currently in "logo.vhd"
2015-01-25 Adding gitignore
2015-01-25 Updating ISE project file from 14.6 to 14.7
2015-01-26 Added dvd_out project
    This project was merged from:
    http://hamsterworks.co.nz/mediawiki/index.php/MiniSpartan6%2B_DVID_Logo
    and
    http://hamsterworks.co.nz/mediawiki/index.php/MiniSpartan6%2B_DVID_Output
    since I was not able to get the later working.
2015-01-26 Fixing CLKIN_PERIOD to 20ns for 50MHz clock
2015-01-26 Removed generated work folders
2015-01-31 cleanup
    - removing generated files
    - moving ipcore to ipcore_dir
2015-01-31 adding edid
    - adding edid slave and rom files from:
    url:
    https://github.com/timvideos/HDMI2USB/tree/master/hdl/edid
    hash: 44cae6dee95853eaf42065bded21160662bbe4d0
2015-02-01 cleanup
    - removing generated files
    - moving ipcore to ipcore_dir
    - changing work folder to work
2015-02-01 adding board pin-out
    - adding image from user jamesots from forum:
    http://www.scarabhardware.com/forums/topic/ms6-board-pinout/
2015-02-01 updating readme file
2015-02-01 diagram update
    - updating diagram from: https://raw.githubusercontent.com/jamesots/learnfpga/master/diagram2.png
2015-02-01 added audio project
    - added code from user nerfninja from http://www.scarabhardware.com/forums/topic/audio-from-the-minispartan/
    - aud_top.v from http://www.codeshare.io/RAKpm
    - aud.ucf from http://www.codeshare.io/pI4lR
2015-02-01 added projects/readme.md and small changes
    - added readme file
    - added *.filter to gitignore
    - updated project file
2015-02-02 code cleanup
    - removing generated files
    - updating gitignore
    - updating project files
    - regenerating cores
2015-02-02 changing input clock to 65mhz
    - edicrom.hex contains settings for 1024x768@60, which has pixel clock 65mhz
    - not working, got broken after cleanup
2015-05-12 Added Copyright to the schematic
    Added Copyright to the schematic
2015-05-12 Copyright File
    Copyright File

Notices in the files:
parts and their libraries:
SparkFun-Connectors: Licensing: CC v3.0 Share-Alike You are welcome to use this library for commercial purposes.
